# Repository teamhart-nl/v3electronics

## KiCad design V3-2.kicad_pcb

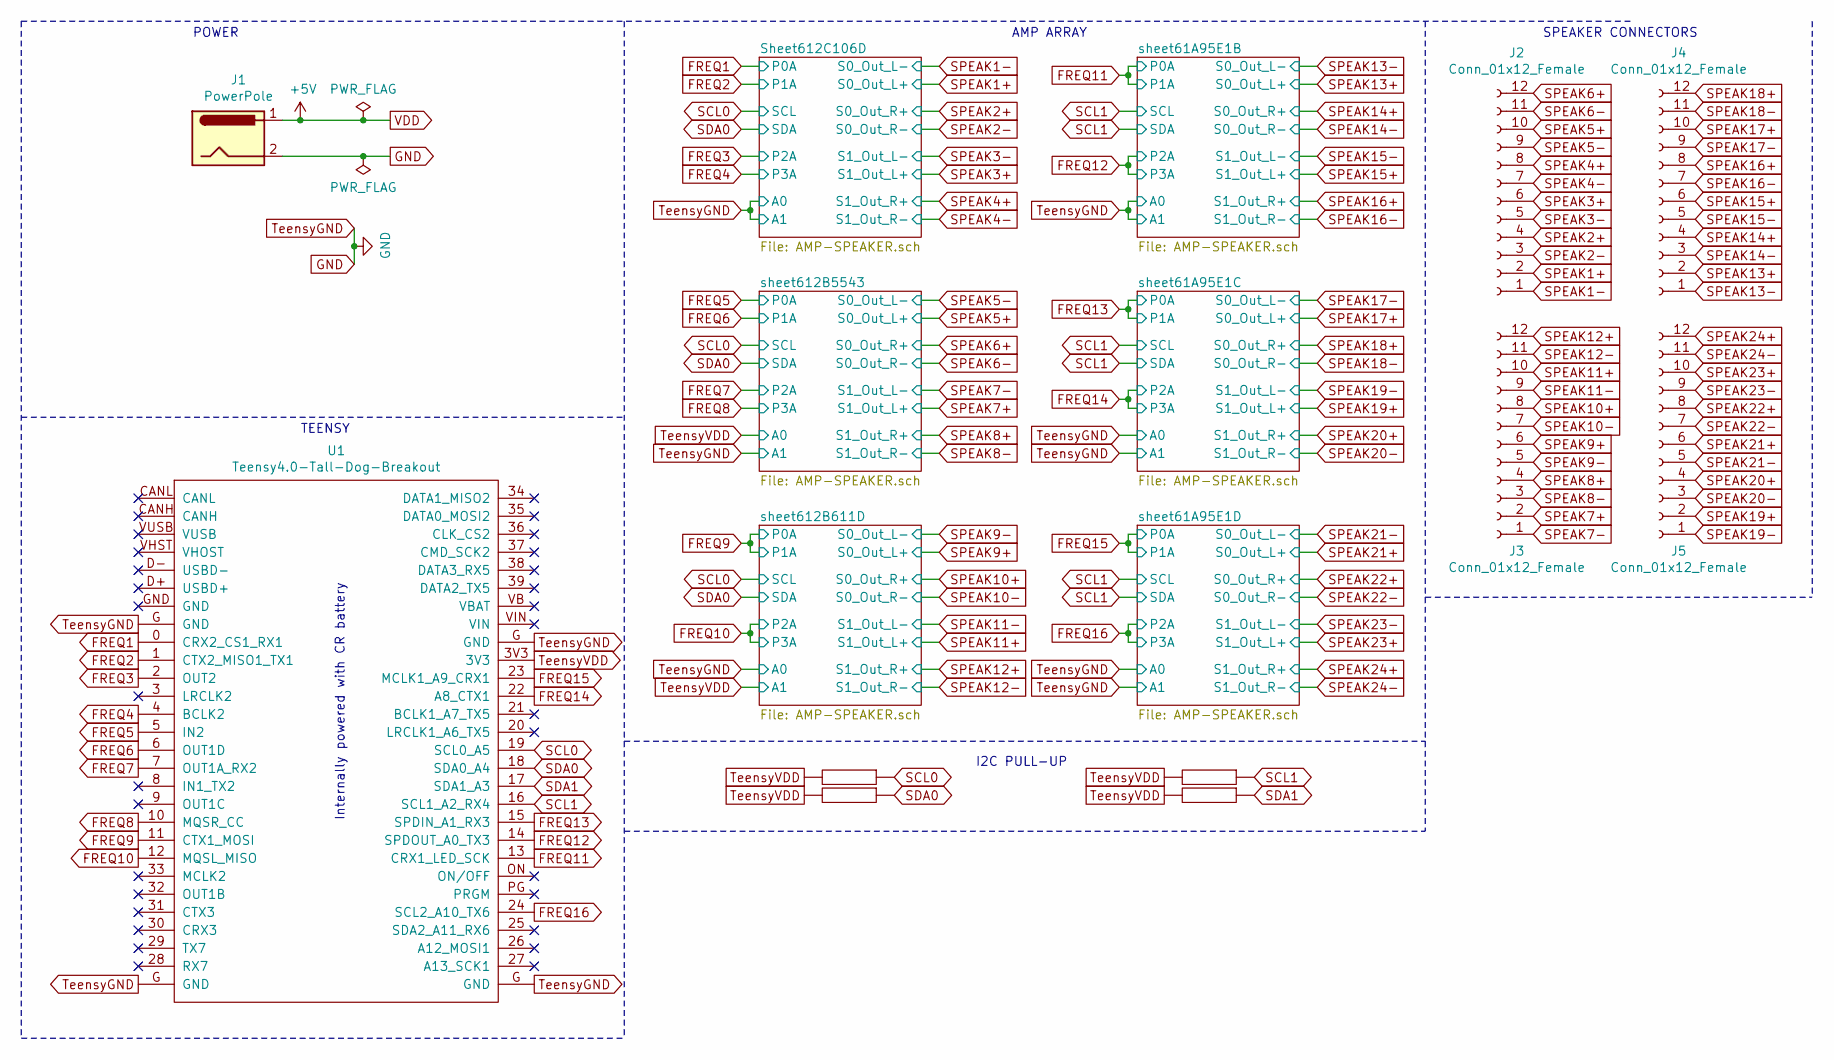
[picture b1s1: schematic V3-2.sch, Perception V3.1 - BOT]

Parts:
J1: PowerPole; 45A-VERT-PAIR
J2, J3, J4, J5: Conn_01x12_Female; PinSocket_2x06_P2.54mm_Vertical
R1, R2, R15, R16: 2200; R_1206_3216Metric_Pad1.30x1.75mm_HandSolder
U1: Teensy4.0-Tall-Dog-Breakout; TallDogTeensy4.0Breakout

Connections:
FREQ1: U1.0 (CRX2_CS1_RX1); also elsewhere on the board
FREQ2: U1.1 (CTX2_MISO1_TX1); also elsewhere on the board
FREQ3: U1.2 (OUT2); also elsewhere on the board
FREQ4: U1.4 (BCLK2); also elsewhere on the board
FREQ5: U1.5 (IN2); also elsewhere on the board
FREQ6: U1.6 (OUT1D); also elsewhere on the board
FREQ7: U1.7 (OUT1A_RX2); also elsewhere on the board
FREQ8: U1.10 (MQSR_CC); also elsewhere on the board
FREQ9: U1.11 (CTX1_MOSI); also elsewhere on the board
FREQ10: U1.12 (MQSL_MISO); also elsewhere on the board
FREQ11: U1.13 (CRX1_LED_SCK); also elsewhere on the board
FREQ12: U1.14 (SPDOUT_A0_TX3); also elsewhere on the board
FREQ13: U1.15 (SPDIN_A1_RX3); also elsewhere on the board
FREQ14: U1.22 (A8_CTX1); also elsewhere on the board
FREQ15: U1.23 (MCLK1_A9_CRX1); also elsewhere on the board
FREQ16: U1.24 (SCL2_A10_TX6); also elsewhere on the board
GND: J1.2, U1.G (GND); also elsewhere on the board
SCL0: R1.1, U1.19 (SCL0_A5); also elsewhere on the board
SCL1: R15.1, U1.16 (SCL1_A2_RX4); also elsewhere on the board
SDA0: R2.1, U1.18 (SDA0_A4); also elsewhere on the board
SDA1: R16.1, U1.17 (SDA1_A3)
SPEAK1+: J2.2; also elsewhere on the board
SPEAK1-: J2.1; also elsewhere on the board
SPEAK2+: J2.4; also elsewhere on the board
SPEAK2-: J2.3; also elsewhere on the board
SPEAK3+: J2.6; also elsewhere on the board
SPEAK3-: J2.5; also elsewhere on the board
SPEAK4+: J2.8; also elsewhere on the board
SPEAK4-: J2.7; also elsewhere on the board
SPEAK5+: J2.10; also elsewhere on the board
SPEAK5-: J2.9; also elsewhere on the board
SPEAK6+: J2.12; also elsewhere on the board
SPEAK6-: J2.11; also elsewhere on the board
SPEAK7+: J3.2; also elsewhere on the board
SPEAK7-: J3.1; also elsewhere on the board
SPEAK8+: J3.4; also elsewhere on the board
SPEAK8-: J3.3; also elsewhere on the board
SPEAK9+: J3.6; also elsewhere on the board
SPEAK9-: J3.5; also elsewhere on the board
SPEAK10+: J3.8; also elsewhere on the board
SPEAK10-: J3.7; also elsewhere on the board
SPEAK11+: J3.10; also elsewhere on the board
SPEAK11-: J3.9; also elsewhere on the board
SPEAK12+: J3.12; also elsewhere on the board
SPEAK12-: J3.11; also elsewhere on the board
SPEAK13+: J4.2; also elsewhere on the board
SPEAK13-: J4.1; also elsewhere on the board
SPEAK14+: J4.4; also elsewhere on the board
SPEAK14-: J4.3; also elsewhere on the board
SPEAK15+: J4.6; also elsewhere on the board
SPEAK15-: J4.5; also elsewhere on the board
SPEAK16+: J4.8; also elsewhere on the board
SPEAK16-: J4.7; also elsewhere on the board
SPEAK17+: J4.10; also elsewhere on the board
SPEAK17-: J4.9; also elsewhere on the board
SPEAK18+: J4.12; also elsewhere on the board
SPEAK18-: J4.11; also elsewhere on the board
SPEAK19+: J5.2; also elsewhere on the board
SPEAK19-: J5.1; also elsewhere on the board
SPEAK20+: J5.4; also elsewhere on the board
SPEAK20-: J5.3; also elsewhere on the board
SPEAK21+: J5.6; also elsewhere on the board
SPEAK21-: J5.5; also elsewhere on the board
SPEAK22+: J5.8; also elsewhere on the board
SPEAK22-: J5.7; also elsewhere on the board
SPEAK23+: J5.10; also elsewhere on the board
SPEAK23-: J5.9; also elsewhere on the board
SPEAK24+: J5.12; also elsewhere on the board
SPEAK24-: J5.11; also elsewhere on the board
TeensyVDD: R1.2, R2.2, R15.2, R16.2, U1.3V3; also elsewhere on the board
VDD: J1.1; also elsewhere on the board

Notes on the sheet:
POWER
TEENSY
SPEAKER CONNECTORS
I2C PULL-UP
Internally powered with CR battery
AMP ARRAY

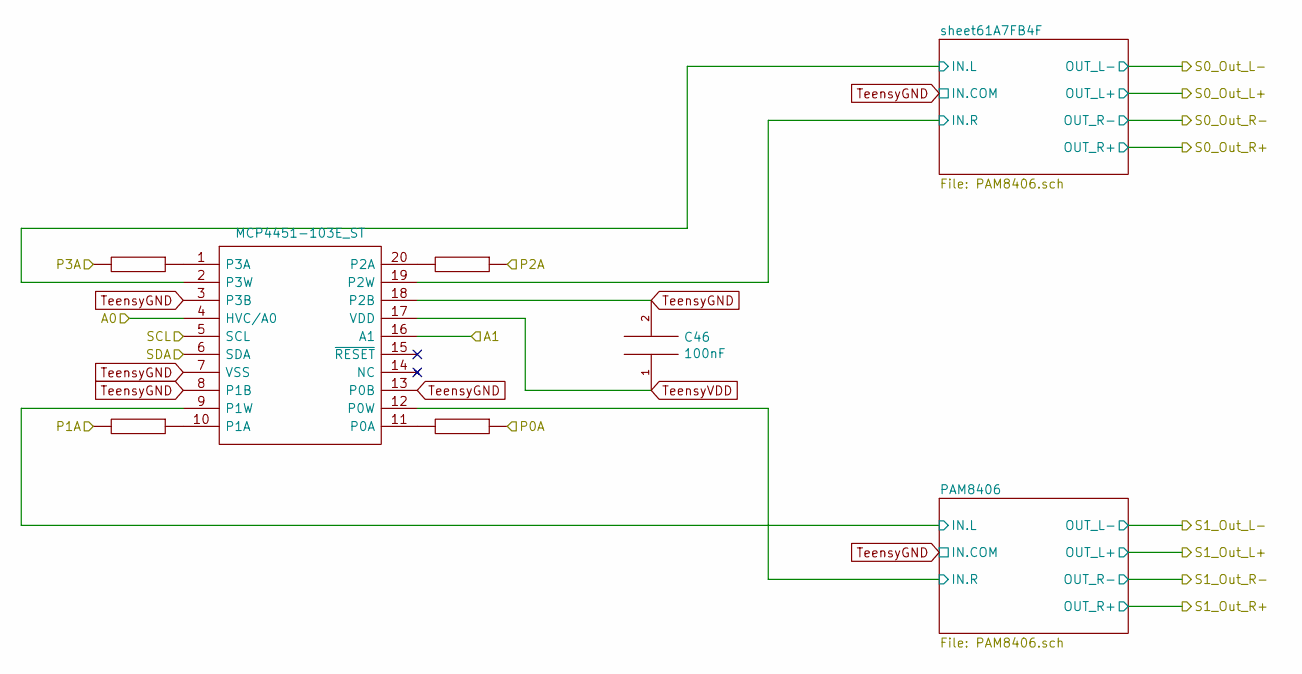
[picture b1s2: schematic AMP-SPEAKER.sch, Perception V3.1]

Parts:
C3: 100nF; C_1206_3216Metric_Pad1.33x1.80mm_HandSolder
IC1: MCP4451-103E_ST; SOP65P640X120-20N; Manufacturer_Part_Number MCP4451-103E/ST; Mouser Part Number 579-MCP4451-103E/ST
R3, R4, R5, R6: 51000; R_1206_3216Metric_Pad1.30x1.75mm_HandSolder

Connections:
/Sheet612C106D/PAM8406/IN.L: IC1.9 (P1W); also elsewhere on the board
/Sheet612C106D/PAM8406/IN.R: IC1.12 (P0W); also elsewhere on the board
/Sheet612C106D/sheet61A7FB4F/IN.L: IC1.2 (P3W); also elsewhere on the board
/Sheet612C106D/sheet61A7FB4F/IN.R: IC1.19 (P2W); also elsewhere on the board
FREQ1: R6.1; also elsewhere on the board
FREQ2: R4.2; also elsewhere on the board
FREQ3: R5.1; also elsewhere on the board
FREQ4: R3.2; also elsewhere on the board
GND: C3.2, IC1.3 (P3B), IC1.4 (HVC/A0), IC1.7 (VSS), IC1.8 (P1B), IC1.13 (P0B), IC1.16 (A1), IC1.18 (P2B); also elsewhere on the board
unnamed: IC1.1 (P3A), R3.1
unnamed: IC1.10 (P1A), R4.1
unnamed: IC1.11 (P0A), R6.2
unnamed: IC1.20 (P2A), R5.2
SCL0: IC1.5 (SCL); also elsewhere on the board
SDA0: IC1.6 (SDA); also elsewhere on the board
TeensyVDD: C3.1, IC1.17 (VDD); also elsewhere on the board

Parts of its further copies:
C1, C2, C28, C37, C46: 100nF; C_1206_3216Metric_Pad1.33x1.80mm_HandSolder
IC2, IC3, IC10, IC13, IC16: MCP4451-103E_ST; SOP65P640X120-20N; Manufacturer_Part_Number MCP4451-103E/ST; Mouser Part Number 579-MCP4451-103E/ST
R7, R8, R9, R10, R11, R12, R13, R14, R17, R18, R19, R20, R21, R22, R23, R24, R25, R26, R27, R28: 51000; R_1206_3216Metric_Pad1.30x1.75mm_HandSolder

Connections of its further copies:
/sheet61A95E1B/PAM8406/IN.L: IC10.9 (P1W); also elsewhere on the board
/sheet61A95E1B/PAM8406/IN.R: IC10.12 (P0W); also elsewhere on the board
/sheet61A95E1B/sheet61A7FB4F/IN.L: IC10.2 (P3W); also elsewhere on the board
/sheet61A95E1B/sheet61A7FB4F/IN.R: IC10.19 (P2W); also elsewhere on the board
/sheet61A95E1C/PAM8406/IN.L: IC13.9 (P1W); also elsewhere on the board
/sheet61A95E1C/PAM8406/IN.R: IC13.12 (P0W); also elsewhere on the board
/sheet61A95E1C/sheet61A7FB4F/IN.L: IC13.2 (P3W); also elsewhere on the board
/sheet61A95E1C/sheet61A7FB4F/IN.R: IC13.19 (P2W); also elsewhere on the board
/sheet61A95E1D/PAM8406/IN.L: IC16.9 (P1W); also elsewhere on the board
/sheet61A95E1D/PAM8406/IN.R: IC16.12 (P0W); also elsewhere on the board
/sheet61A95E1D/sheet61A7FB4F/IN.L: IC16.2 (P3W); also elsewhere on the board
/sheet61A95E1D/sheet61A7FB4F/IN.R: IC16.19 (P2W); also elsewhere on the board
/sheet612B611D/PAM8406/IN.L: IC3.9 (P1W); also elsewhere on the board
/sheet612B611D/PAM8406/IN.R: IC3.12 (P0W); also elsewhere on the board
/sheet612B611D/sheet61A7FB4F/IN.L: IC3.2 (P3W); also elsewhere on the board
/sheet612B611D/sheet61A7FB4F/IN.R: IC3.19 (P2W); also elsewhere on the board
/sheet612B5543/PAM8406/IN.L: IC2.9 (P1W); also elsewhere on the board
/sheet612B5543/PAM8406/IN.R: IC2.12 (P0W); also elsewhere on the board
/sheet612B5543/sheet61A7FB4F/IN.L: IC2.2 (P3W); also elsewhere on the board
/sheet612B5543/sheet61A7FB4F/IN.R: IC2.19 (P2W); also elsewhere on the board
FREQ5: R10.1; also elsewhere on the board
FREQ6: R8.2; also elsewhere on the board
FREQ7: R9.1; also elsewhere on the board
FREQ8: R7.2; also elsewhere on the board
FREQ9: R12.2, R14.1; also elsewhere on the board
FREQ10: R11.2, R13.1; also elsewhere on the board
FREQ11: R18.2, R20.1; also elsewhere on the board
FREQ12: R17.2, R19.1; also elsewhere on the board
FREQ13: R22.2, R24.1; also elsewhere on the board
FREQ14: R21.2, R23.1; also elsewhere on the board
FREQ15: R26.2, R28.1; also elsewhere on the board
FREQ16: R25.2, R27.1; also elsewhere on the board
GND: C1.2, C2.2, C28.2, C37.2, C46.2, IC2.3 (P3B), IC2.7 (VSS), IC2.8 (P1B), IC2.13 (P0B), IC2.16 (A1), IC2.18 (P2B), IC3.3 (P3B), IC3.4 (HVC/A0), IC3.7 (VSS), IC3.8 (P1B), IC3.13 (P0B), IC3.18 (P2B), IC10.3 (P3B), IC10.4 (HVC/A0), IC10.7 (VSS), IC10.8 (P1B), IC10.13 (P0B), IC10.16 (A1), IC10.18 (P2B), IC13.3 (P3B), IC13.4 (HVC/A0), IC13.7 (VSS), IC13.8 (P1B), IC13.13 (P0B), IC13.16 (A1), IC13.18 (P2B), IC16.3 (P3B), IC16.4 (HVC/A0), IC16.7 (VSS), IC16.8 (P1B), IC16.13 (P0B), IC16.16 (A1), IC16.18 (P2B); also elsewhere on the board
unnamed: IC2.1 (P3A), R7.1
unnamed: IC2.10 (P1A), R8.1
unnamed: IC2.11 (P0A), R10.2
unnamed: IC2.20 (P2A), R9.2
unnamed: IC3.1 (P3A), R11.1
unnamed: IC3.10 (P1A), R12.1
unnamed: IC3.11 (P0A), R14.2
unnamed: IC3.20 (P2A), R13.2
unnamed: IC10.1 (P3A), R17.1
unnamed: IC10.10 (P1A), R18.1
unnamed: IC10.11 (P0A), R20.2
unnamed: IC10.20 (P2A), R19.2
unnamed: IC13.1 (P3A), R21.1
unnamed: IC13.10 (P1A), R22.1
unnamed: IC13.11 (P0A), R24.2
unnamed: IC13.20 (P2A), R23.2
unnamed: IC16.1 (P3A), R25.1
unnamed: IC16.10 (P1A), R26.1
unnamed: IC16.11 (P0A), R28.2
unnamed: IC16.20 (P2A), R27.2
SCL0: IC2.5 (SCL), IC3.5 (SCL); also elsewhere on the board
SCL1: IC10.5 (SCL), IC10.6 (SDA), IC13.5 (SCL), IC13.6 (SDA), IC16.5 (SCL), IC16.6 (SDA); also elsewhere on the board
SDA0: IC2.6 (SDA), IC3.6 (SDA); also elsewhere on the board
TeensyVDD: C1.1, C2.1, C28.1, C37.1, C46.1, IC2.4 (HVC/A0), IC2.17 (VDD), IC3.16 (A1), IC3.17 (VDD), IC10.17 (VDD), IC13.17 (VDD), IC16.17 (VDD); also elsewhere on the board

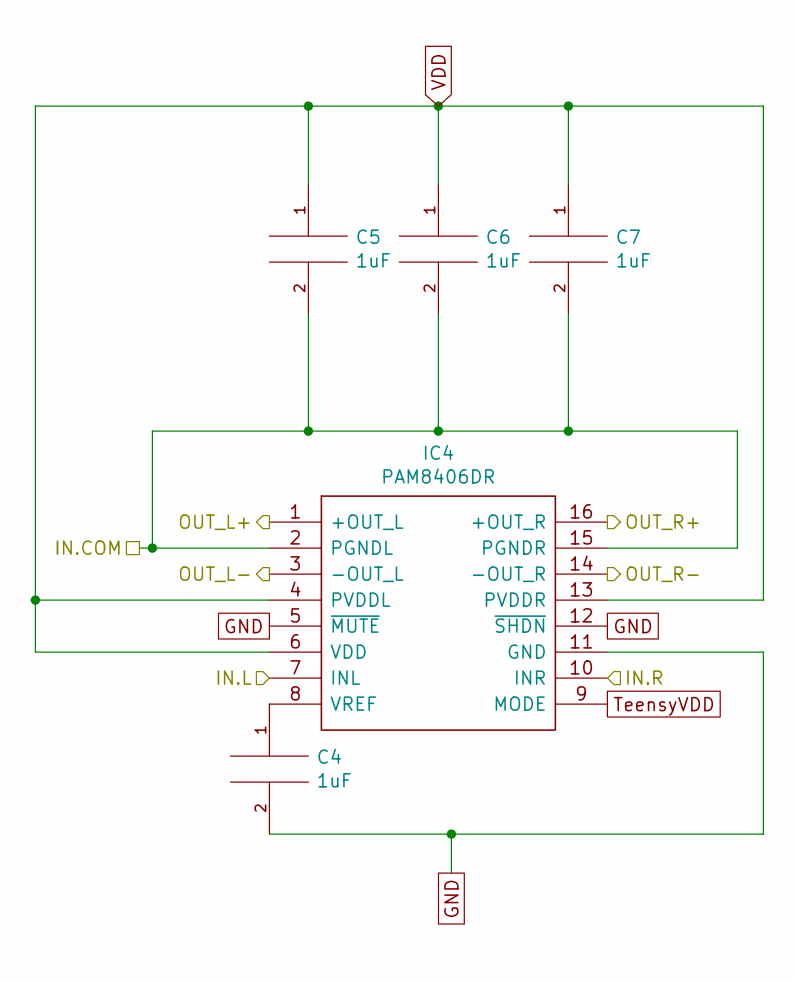
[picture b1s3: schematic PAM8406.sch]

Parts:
C4, C5, C6, C7: 1uF; C_1206_3216Metric_Pad1.33x1.80mm_HandSolder
IC4: PAM8406DR; SOIC127P605X175-16N; Manufacturer_Part_Number PAM8406DR; Mouser Part Number 621-PAM8406DR

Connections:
/Sheet612C106D/PAM8406/IN.L: IC4.7 (INL); also elsewhere on the board
/Sheet612C106D/PAM8406/IN.R: IC4.10 (INR); also elsewhere on the board
GND: C4.2, C5.2, C6.2, C7.2, IC4.2 (PGNDL), IC4.5 (~MUTE), IC4.11 (GND), IC4.12 (~SHDN), IC4.15 (PGNDR); also elsewhere on the board
unnamed: C4.1, IC4.8 (VREF)
SPEAK3+: IC4.1 (+OUT_L); also elsewhere on the board
SPEAK3-: IC4.3 (-OUT_L); also elsewhere on the board
SPEAK4+: IC4.16 (+OUT_R); also elsewhere on the board
SPEAK4-: IC4.14 (-OUT_R); also elsewhere on the board
TeensyVDD: IC4.9 (MODE); also elsewhere on the board
VDD: C5.1, C6.1, C7.1, IC4.4 (PVDDL), IC4.6 (VDD), IC4.13 (PVDDR); also elsewhere on the board

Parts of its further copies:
C8, C9, C10, C11, C12, C13, C14, C15, C16, C17, C18, C19, C20, C21, C22, C23, C24, C25, C26, C27, C29, C30, C31, C32, C33, C34, C35, C36, C38, C39, C40, C41, C42, C43, C44, C45, C47, C48, C49, C50, C51, C52, C53, C54: 1uF; C_1206_3216Metric_Pad1.33x1.80mm_HandSolder
IC5, IC6, IC7, IC8, IC9, IC11, IC12, IC14, IC15, IC17, IC18: PAM8406DR; SOIC127P605X175-16N; Manufacturer_Part_Number PAM8406DR; Mouser Part Number 621-PAM8406DR

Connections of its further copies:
/Sheet612C106D/sheet61A7FB4F/IN.L: IC5.7 (INL); also elsewhere on the board
/Sheet612C106D/sheet61A7FB4F/IN.R: IC5.10 (INR); also elsewhere on the board
/sheet61A95E1B/PAM8406/IN.L: IC11.7 (INL); also elsewhere on the board
/sheet61A95E1B/PAM8406/IN.R: IC11.10 (INR); also elsewhere on the board
/sheet61A95E1B/sheet61A7FB4F/IN.L: IC12.7 (INL); also elsewhere on the board
/sheet61A95E1B/sheet61A7FB4F/IN.R: IC12.10 (INR); also elsewhere on the board
/sheet61A95E1C/PAM8406/IN.L: IC14.7 (INL); also elsewhere on the board
/sheet61A95E1C/PAM8406/IN.R: IC14.10 (INR); also elsewhere on the board
/sheet61A95E1C/sheet61A7FB4F/IN.L: IC15.7 (INL); also elsewhere on the board
/sheet61A95E1C/sheet61A7FB4F/IN.R: IC15.10 (INR); also elsewhere on the board
/sheet61A95E1D/PAM8406/IN.L: IC17.7 (INL); also elsewhere on the board
/sheet61A95E1D/PAM8406/IN.R: IC17.10 (INR); also elsewhere on the board
/sheet61A95E1D/sheet61A7FB4F/IN.L: IC18.7 (INL); also elsewhere on the board
/sheet61A95E1D/sheet61A7FB4F/IN.R: IC18.10 (INR); also elsewhere on the board
/sheet612B611D/PAM8406/IN.L: IC8.7 (INL); also elsewhere on the board
/sheet612B611D/PAM8406/IN.R: IC8.10 (INR); also elsewhere on the board
/sheet612B611D/sheet61A7FB4F/IN.L: IC9.7 (INL); also elsewhere on the board
/sheet612B611D/sheet61A7FB4F/IN.R: IC9.10 (INR); also elsewhere on the board
/sheet612B5543/PAM8406/IN.L: IC6.7 (INL); also elsewhere on the board
/sheet612B5543/PAM8406/IN.R: IC6.10 (INR); also elsewhere on the board
/sheet612B5543/sheet61A7FB4F/IN.L: IC7.7 (INL); also elsewhere on the board
/sheet612B5543/sheet61A7FB4F/IN.R: IC7.10 (INR); also elsewhere on the board
GND: C8.2, C9.2, C10.2, C11.2, C12.2, C13.2, C14.2, C15.2, C16.2, C17.2, C18.2, C19.2, C20.2, C21.2, C22.2, C23.2, C24.2, C25.2, C26.2, C27.2, C29.2, C30.2, C31.2, C32.2, C33.2, C34.2, C35.2, C36.2, C38.2, C39.2, C40.2, C41.2, C42.2, C43.2, C44.2, C45.2, C47.2, C48.2, C49.2, C50.2, C51.2, C52.2, C53.2, C54.2, IC5.2 (PGNDL), IC5.5 (~MUTE), IC5.11 (GND), IC5.12 (~SHDN), IC5.15 (PGNDR), IC6.2 (PGNDL), IC6.5 (~MUTE), IC6.11 (GND), IC6.12 (~SHDN), IC6.15 (PGNDR), IC7.2 (PGNDL), IC7.5 (~MUTE), IC7.11 (GND), IC7.12 (~SHDN), IC7.15 (PGNDR), IC8.2 (PGNDL), IC8.5 (~MUTE), IC8.11 (GND), IC8.12 (~SHDN), IC8.15 (PGNDR), IC9.2 (PGNDL), IC9.5 (~MUTE), IC9.11 (GND), IC9.12 (~SHDN), IC9.15 (PGNDR), IC11.2 (PGNDL), IC11.5 (~MUTE), IC11.11 (GND), IC11.12 (~SHDN), IC11.15 (PGNDR), IC12.2 (PGNDL), IC12.5 (~MUTE), IC12.11 (GND), IC12.12 (~SHDN), IC12.15 (PGNDR), IC14.2 (PGNDL), IC14.5 (~MUTE), IC14.11 (GND), IC14.12 (~SHDN), IC14.15 (PGNDR), IC15.2 (PGNDL), IC15.5 (~MUTE), IC15.11 (GND), IC15.12 (~SHDN), IC15.15 (PGNDR), IC17.2 (PGNDL), IC17.5 (~MUTE), IC17.11 (GND), IC17.12 (~SHDN), IC17.15 (PGNDR), IC18.2 (PGNDL), IC18.5 (~MUTE), IC18.11 (GND), IC18.12 (~SHDN), IC18.15 (PGNDR); also elsewhere on the board
unnamed: C8.1, IC5.8 (VREF)
unnamed: C12.1, IC6.8 (VREF)
unnamed: C16.1, IC7.8 (VREF)
unnamed: C20.1, IC8.8 (VREF)
unnamed: C24.1, IC9.8 (VREF)
unnamed: C29.1, IC11.8 (VREF)
unnamed: C33.1, IC12.8 (VREF)
unnamed: C38.1, IC14.8 (VREF)
unnamed: C42.1, IC15.8 (VREF)
unnamed: C47.1, IC17.8 (VREF)
unnamed: C51.1, IC18.8 (VREF)
SPEAK1+: IC5.1 (+OUT_L); also elsewhere on the board
SPEAK1-: IC5.3 (-OUT_L); also elsewhere on the board
SPEAK2+: IC5.16 (+OUT_R); also elsewhere on the board
SPEAK2-: IC5.14 (-OUT_R); also elsewhere on the board
SPEAK5+: IC7.1 (+OUT_L); also elsewhere on the board
SPEAK5-: IC7.3 (-OUT_L); also elsewhere on the board
SPEAK6+: IC7.16 (+OUT_R); also elsewhere on the board
SPEAK6-: IC7.14 (-OUT_R); also elsewhere on the board
SPEAK7+: IC6.1 (+OUT_L); also elsewhere on the board
SPEAK7-: IC6.3 (-OUT_L); also elsewhere on the board
SPEAK8+: IC6.16 (+OUT_R); also elsewhere on the board
SPEAK8-: IC6.14 (-OUT_R); also elsewhere on the board
SPEAK9+: IC9.1 (+OUT_L); also elsewhere on the board
SPEAK9-: IC9.3 (-OUT_L); also elsewhere on the board
SPEAK10+: IC9.16 (+OUT_R); also elsewhere on the board
SPEAK10-: IC9.14 (-OUT_R); also elsewhere on the board
SPEAK11+: IC8.1 (+OUT_L); also elsewhere on the board
SPEAK11-: IC8.3 (-OUT_L); also elsewhere on the board
SPEAK12+: IC8.16 (+OUT_R); also elsewhere on the board
SPEAK12-: IC8.14 (-OUT_R); also elsewhere on the board
SPEAK13+: IC12.1 (+OUT_L); also elsewhere on the board
SPEAK13-: IC12.3 (-OUT_L); also elsewhere on the board
SPEAK14+: IC12.16 (+OUT_R); also elsewhere on the board
SPEAK14-: IC12.14 (-OUT_R); also elsewhere on the board
SPEAK15+: IC11.1 (+OUT_L); also elsewhere on the board
SPEAK15-: IC11.3 (-OUT_L); also elsewhere on the board
SPEAK16+: IC11.16 (+OUT_R); also elsewhere on the board
SPEAK16-: IC11.14 (-OUT_R); also elsewhere on the board
SPEAK17+: IC15.1 (+OUT_L); also elsewhere on the board
SPEAK17-: IC15.3 (-OUT_L); also elsewhere on the board
SPEAK18+: IC15.16 (+OUT_R); also elsewhere on the board
SPEAK18-: IC15.14 (-OUT_R); also elsewhere on the board
SPEAK19+: IC14.1 (+OUT_L); also elsewhere on the board
SPEAK19-: IC14.3 (-OUT_L); also elsewhere on the board
SPEAK20+: IC14.16 (+OUT_R); also elsewhere on the board
SPEAK20-: IC14.14 (-OUT_R); also elsewhere on the board
SPEAK21+: IC18.1 (+OUT_L); also elsewhere on the board
SPEAK21-: IC18.3 (-OUT_L); also elsewhere on the board
SPEAK22+: IC18.16 (+OUT_R); also elsewhere on the board
SPEAK22-: IC18.14 (-OUT_R); also elsewhere on the board
SPEAK23+: IC17.1 (+OUT_L); also elsewhere on the board
SPEAK23-: IC17.3 (-OUT_L); also elsewhere on the board
SPEAK24+: IC17.16 (+OUT_R); also elsewhere on the board
SPEAK24-: IC17.14 (-OUT_R); also elsewhere on the board
TeensyVDD: IC5.9 (MODE), IC6.9 (MODE), IC7.9 (MODE), IC8.9 (MODE), IC9.9 (MODE), IC11.9 (MODE), IC12.9 (MODE), IC14.9 (MODE), IC15.9 (MODE), IC17.9 (MODE), IC18.9 (MODE); also elsewhere on the board
VDD: C9.1, C10.1, C11.1, C13.1, C14.1, C15.1, C17.1, C18.1, C19.1, C21.1, C22.1, C23.1, C25.1, C26.1, C27.1, C30.1, C31.1, C32.1, C34.1, C35.1, C36.1, C39.1, C40.1, C41.1, C43.1, C44.1, C45.1, C48.1, C49.1, C50.1, C52.1, C53.1, C54.1, IC5.4 (PVDDL), IC5.6 (VDD), IC5.13 (PVDDR), IC6.4 (PVDDL), IC6.6 (VDD), IC6.13 (PVDDR), IC7.4 (PVDDL), IC7.6 (VDD), IC7.13 (PVDDR), IC8.4 (PVDDL), IC8.6 (VDD), IC8.13 (PVDDR), IC9.4 (PVDDL), IC9.6 (VDD), IC9.13 (PVDDR), IC11.4 (PVDDL), IC11.6 (VDD), IC11.13 (PVDDR), IC12.4 (PVDDL), IC12.6 (VDD), IC12.13 (PVDDR), IC14.4 (PVDDL), IC14.6 (VDD), IC14.13 (PVDDR), IC15.4 (PVDDL), IC15.6 (VDD), IC15.13 (PVDDR), IC17.4 (PVDDL), IC17.6 (VDD), IC17.13 (PVDDR), IC18.4 (PVDDL), IC18.6 (VDD), IC18.13 (PVDDR); also elsewhere on the board

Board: 4 copper layers, 106 parts (0 on the bottom side), 131 nets, no tracks yet.

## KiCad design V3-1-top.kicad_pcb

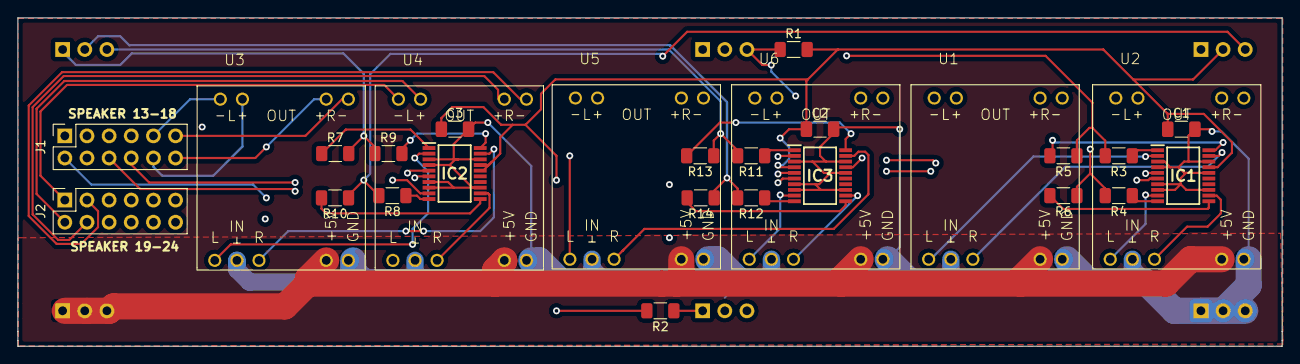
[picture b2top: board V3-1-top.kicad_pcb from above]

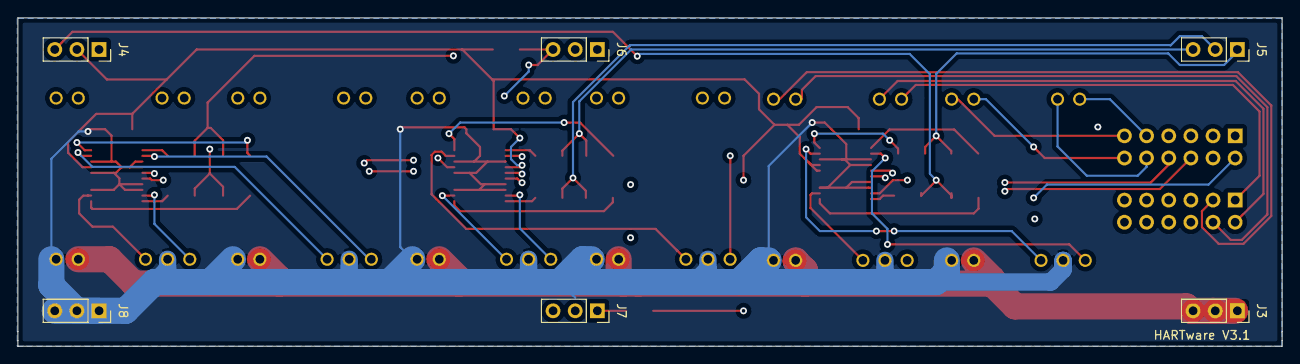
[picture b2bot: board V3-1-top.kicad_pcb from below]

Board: 4 copper layers, 145.0 x 37.7 mm, 34 parts (6 on the bottom side), 59 nets.

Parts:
C1, C2, C3: 100nF; C_1206_3216Metric_Pad1.33x1.80mm_HandSolder
IC1, IC2, IC3: MCP4451-103E_ST; SOP65P640X120-20N
J1, J2: Conn_01x12_Female; PinSocket_2x06_P2.54mm_Vertical
J3, J4, J5, J6, J7, J8: Conn_01x03_Male; PinSocket_1x03_P2.54mm_Vertical
R1, R2: 2200; R_1206_3216Metric_Pad1.30x1.75mm_HandSolder
R3, R4, R5, R6, R7, R8, R9, R10, R11, R12, R13, R14: 51000; R_1206_3216Metric_Pad1.30x1.75mm_HandSolder
U1, U2, U3, U4, U5, U6: AMPLIFIER-PAM8403

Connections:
FREQ11: J6.1, R4.2, R6.1
FREQ12: J6.2, R3.2, R5.1
FREQ13: J4.3, R8.2, R10.1
FREQ14: J5.1, R7.2, R9.1
FREQ15: J5.2, R12.2, R14.1
FREQ16: J5.3, R11.2, R13.1
GND: C1.2, C2.2, C3.2, IC1.3, IC1.4, IC1.7, IC1.8, IC1.13, IC1.16, IC1.18, IC2.3, IC2.4, IC2.7, IC2.8, IC2.13, IC2.18, IC3.3, IC3.7, IC3.8, IC3.13, IC3.16, IC3.18, J8.1, J8.2, J8.3, U1.GND, U1.IN.COM, U2.GND, U2.IN.COM, U3.GND, U3.IN.COM, U4.GND, U4.IN.COM, U5.GND, U5.IN.COM, U6.GND, U6.IN.COM
unnamed: IC1.1, R3.1
unnamed: IC1.2, U1.IN.L
unnamed: IC1.9, U2.IN.L
unnamed: IC1.10, R4.1
unnamed: IC1.11, R6.2
unnamed: IC1.12, U2.IN.R
unnamed: IC1.19, U1.IN.R
unnamed: IC1.20, R5.2
unnamed: IC2.1, R7.1
unnamed: IC2.2, U3.IN.L
unnamed: IC2.9, U4.IN.L
unnamed: IC2.10, R8.1
unnamed: IC2.11, R10.2
unnamed: IC2.12, U4.IN.R
unnamed: IC2.19, U3.IN.R
unnamed: IC2.20, R9.2
unnamed: IC3.1, R11.1
unnamed: IC3.2, U5.IN.L
unnamed: IC3.9, U6.IN.L
unnamed: IC3.10, R12.1
unnamed: IC3.11, R14.2
unnamed: IC3.12, U6.IN.R
unnamed: IC3.19, U5.IN.R
unnamed: IC3.20, R13.2
SCL1: IC1.5, IC2.5, IC3.5, J7.1, R2.1
SDA1: IC1.6, IC2.6, IC3.6, J6.3, R1.1
SPEAK13+: J1.2, U1.OUT.L+
SPEAK13-: J1.1, U1.OUT.L-
SPEAK14+: J1.4, U1.OUT.R+
SPEAK14-: J1.3, U1.OUT.R-
SPEAK15+: J1.6, U2.OUT.L+
SPEAK15-: J1.5, U2.OUT.L-
SPEAK16+: J1.8, U2.OUT.R+
SPEAK16-: J1.7, U2.OUT.R-
SPEAK17+: J1.10, U3.OUT.L+
SPEAK17-: J1.9, U3.OUT.L-
SPEAK18+: J1.12, U3.OUT.R+
SPEAK18-: J1.11, U3.OUT.R-
SPEAK19+: J2.2, U4.OUT.L+
SPEAK19-: J2.1, U4.OUT.L-
SPEAK20+: J2.4, U4.OUT.R+
SPEAK20-: J2.3, U4.OUT.R-
SPEAK21+: J2.6, U5.OUT.L+
SPEAK21-: J2.5, U5.OUT.L-
SPEAK22+: J2.8, U5.OUT.R+
SPEAK22-: J2.7, U5.OUT.R-
SPEAK23+: J2.10, U6.OUT.L+
SPEAK23-: J2.9, U6.OUT.L-
SPEAK24+: J2.12, U6.OUT.R+
SPEAK24-: J2.11, U6.OUT.R-
TeensyVDD: C1.1, C2.1, C3.1, IC1.17, IC2.16, IC2.17, IC3.4, IC3.17, J4.2, R1.2, R2.2
VDD: J3.1, J3.2, J3.3, U1.+5V, U2.+5V, U3.+5V, U4.+5V, U5.+5V, U6.+5V

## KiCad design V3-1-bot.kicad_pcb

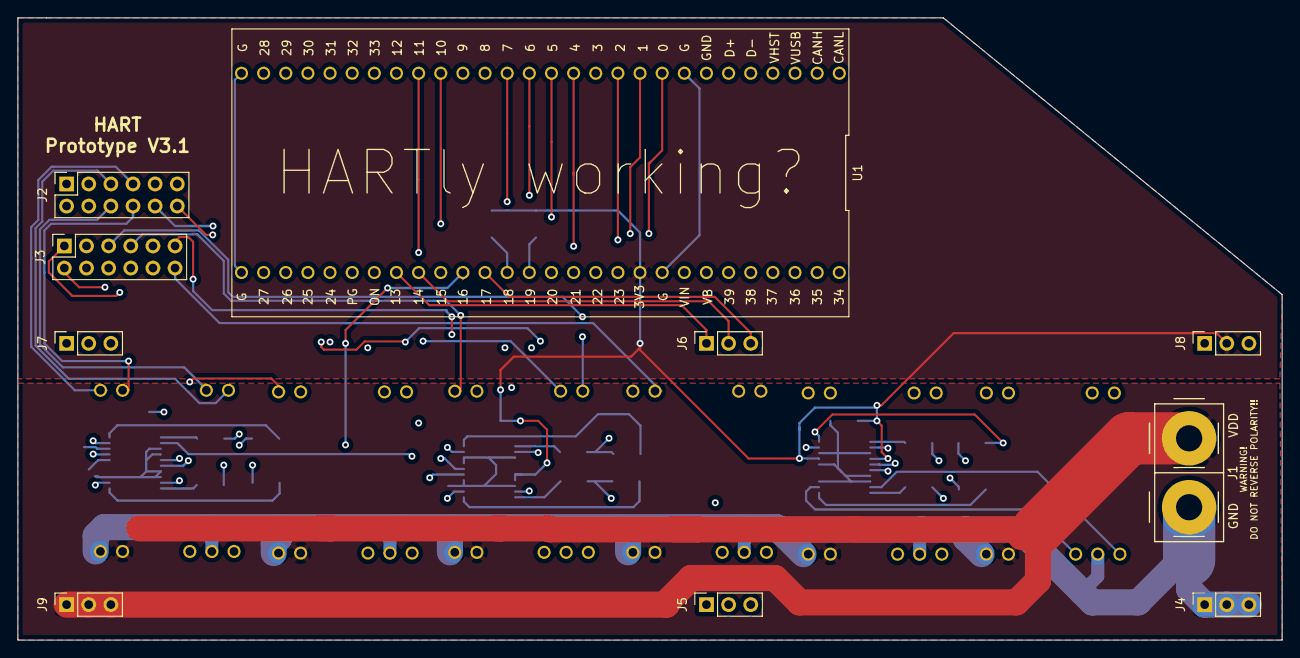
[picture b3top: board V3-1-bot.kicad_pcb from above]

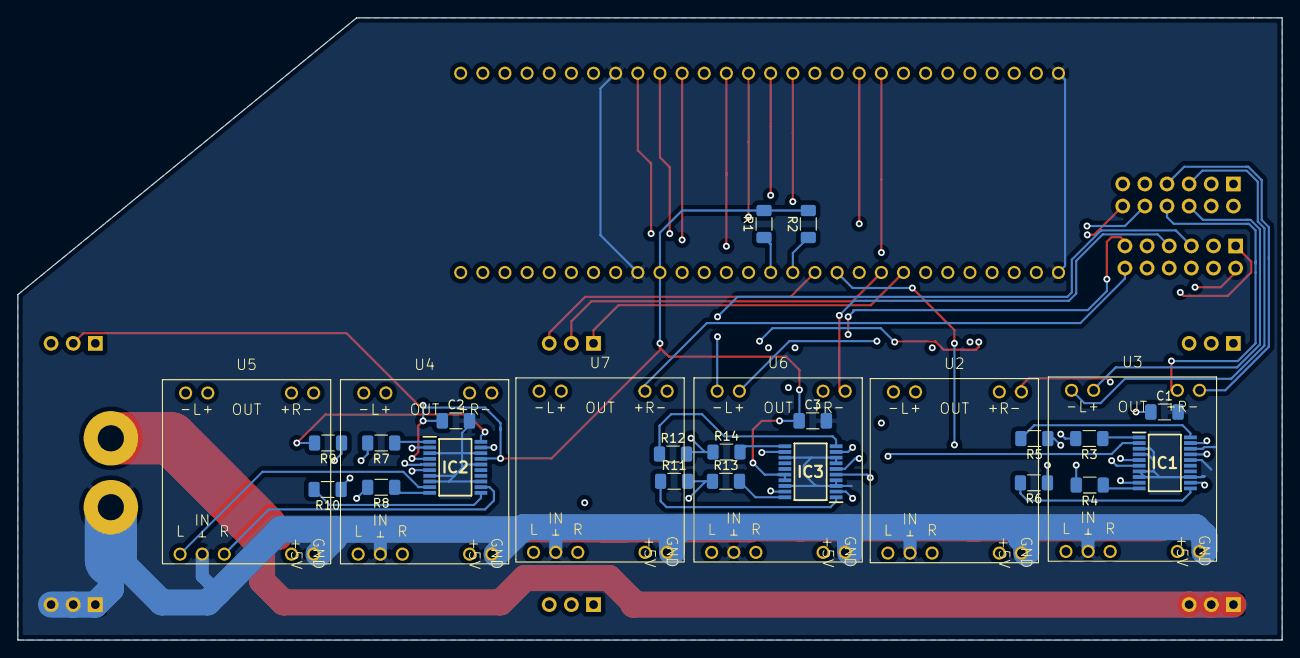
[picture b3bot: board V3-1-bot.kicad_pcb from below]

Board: 4 copper layers, 145.0 x 71.4 mm, 36 parts (26 on the bottom side), 71 nets.

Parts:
C1, C2, C3: 100nF; C_1206_3216Metric_Pad1.33x1.80mm_HandSolder
IC1, IC2, IC3: MCP4451-103E_ST; SOP65P640X120-20N
J1: PowerPole; 45A-VERT-PAIR
J2, J3: Conn_01x12_Female; PinSocket_2x06_P2.54mm_Vertical
J4, J5, J6, J7, J8, J9: Conn_01x03_Female; PinSocket_1x03_P2.54mm_Vertical
R1, R2: 2200; R_1206_3216Metric_Pad1.30x1.75mm_HandSolder
R3, R4, R5, R6, R7, R8, R9, R10, R11, R12, R13, R14: 51000; R_1206_3216Metric_Pad1.30x1.75mm_HandSolder
U1: Teensy4.0-Tall-Dog-Breakout; TallDogTeensy4.0Breakout
U2, U3, U4, U5, U6, U7: AMPLIFIER-PAM8403

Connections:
FREQ1: R6.1, U1.0
FREQ2: R4.2, U1.1
FREQ3: R5.1, U1.2
FREQ4: R3.2, U1.4
FREQ5: R10.1, U1.5
FREQ6: R8.2, U1.6
FREQ7: R9.1, U1.7
FREQ8: R7.2, U1.10
FREQ9: R12.2, R14.1, U1.11
FREQ10: R11.2, R13.1, U1.12
FREQ11: J6.1, U1.13
FREQ12: J6.2, U1.14
FREQ13: J8.3, U1.15
FREQ14: J7.1, U1.22
FREQ15: J7.2, U1.23
FREQ16: J7.3, U1.24
GND: C1.2, C2.2, C3.2, IC1.3, IC1.4, IC1.7, IC1.8, IC1.13, IC1.16, IC1.18, IC2.3, IC2.7, IC2.8, IC2.13, IC2.16, IC2.18, IC3.3, IC3.4, IC3.7, IC3.8, IC3.13, IC3.18, J1.2, J4.1, J4.2, J4.3, U1.G, U2.GND, U2.IN.COM, U3.GND, U3.IN.COM, U4.GND, U4.IN.COM, U5.GND, U5.IN.COM, U6.GND, U6.IN.COM, U7.GND, U7.IN.COM
unnamed: IC1.1, R3.1
unnamed: IC1.2, U2.IN.L
unnamed: IC1.9, U3.IN.L
unnamed: IC1.10, R4.1
unnamed: IC1.11, R6.2
unnamed: IC1.12, U3.IN.R
unnamed: IC1.19, U2.IN.R
unnamed: IC1.20, R5.2
unnamed: IC2.1, R7.1
unnamed: IC2.2, U4.IN.L
unnamed: IC2.9, U5.IN.L
unnamed: IC2.10, R8.1
unnamed: IC2.11, R10.2
unnamed: IC2.12, U5.IN.R
unnamed: IC2.19, U4.IN.R
unnamed: IC2.20, R9.2
unnamed: IC3.1, R11.1
unnamed: IC3.2, U6.IN.L
unnamed: IC3.9, U7.IN.L
unnamed: IC3.10, R12.1
unnamed: IC3.11, R14.2
unnamed: IC3.12, U7.IN.R
unnamed: IC3.19, U6.IN.R
unnamed: IC3.20, R13.2
SCL0: IC1.5, IC2.5, IC3.5, R1.1, U1.19
SCL1: J5.1, U1.16
SDA0: IC1.6, IC2.6, IC3.6, R2.1, U1.18
SDA1: J6.3, U1.17
SPEAK1+: J2.2, U2.OUT.L+
SPEAK1-: J2.1, U2.OUT.L-
SPEAK2+: J2.4, U2.OUT.R+
SPEAK2-: J2.3, U2.OUT.R-
SPEAK3+: J2.6, U3.OUT.L+
SPEAK3-: J2.5, U3.OUT.L-
SPEAK4+: J2.8, U3.OUT.R+
SPEAK4-: J2.7, U3.OUT.R-
SPEAK5+: J2.10, U4.OUT.L+
SPEAK5-: J2.9, U4.OUT.L-
SPEAK6+: J2.12, U4.OUT.R+
SPEAK6-: J2.11, U4.OUT.R-
SPEAK7+: J3.2, U5.OUT.L+
SPEAK7-: J3.1, U5.OUT.L-
SPEAK8+: J3.4, U5.OUT.R+
SPEAK8-: J3.3, U5.OUT.R-
SPEAK9+: J3.6, U6.OUT.L+
SPEAK9-: J3.5, U6.OUT.L-
SPEAK10+: J3.8, U6.OUT.R+
SPEAK10-: J3.7, U6.OUT.R-
SPEAK11+: J3.10, U7.OUT.L+
SPEAK11-: J3.9, U7.OUT.L-
SPEAK12+: J3.12, U7.OUT.R+
SPEAK12-: J3.11, U7.OUT.R-
TeensyVDD: C1.1, C2.1, C3.1, IC1.17, IC2.4, IC2.17, IC3.16, IC3.17, J8.2, R1.2, R2.2, U1.3V3
VDD: J1.1, J9.1, J9.2, J9.3, U2.+5V, U3.+5V, U4.+5V, U5.+5V, U6.+5V, U7.+5V
